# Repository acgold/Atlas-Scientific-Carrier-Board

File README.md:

# Atlas Scientific Carrier Board

This repository has Gerber files and a KiCad file for an Atlas Scientific chip carrier board. This board was designed to work with a Mayfly data logger from https://www.envirodiy.org/. Solder on female headers to plug in the sensor chips and inline voltage isolators. Voltage isolators are necessary, but you could use some jumper wires if you don't want to use a voltage isolator. The "EN" and "GND" at the top left allow you to attach a two-pin connector and set the voltage isolators to energy-saving mode (untested). A grove socket can be soldered onto the top of the board to allow easy communication using a grove cable. BNC connectors that connect to the sensors directly can be soldered on the bottom of the board, or use another three-pin connector. Three of these boards cost about $25 at https://oshpark.com/.

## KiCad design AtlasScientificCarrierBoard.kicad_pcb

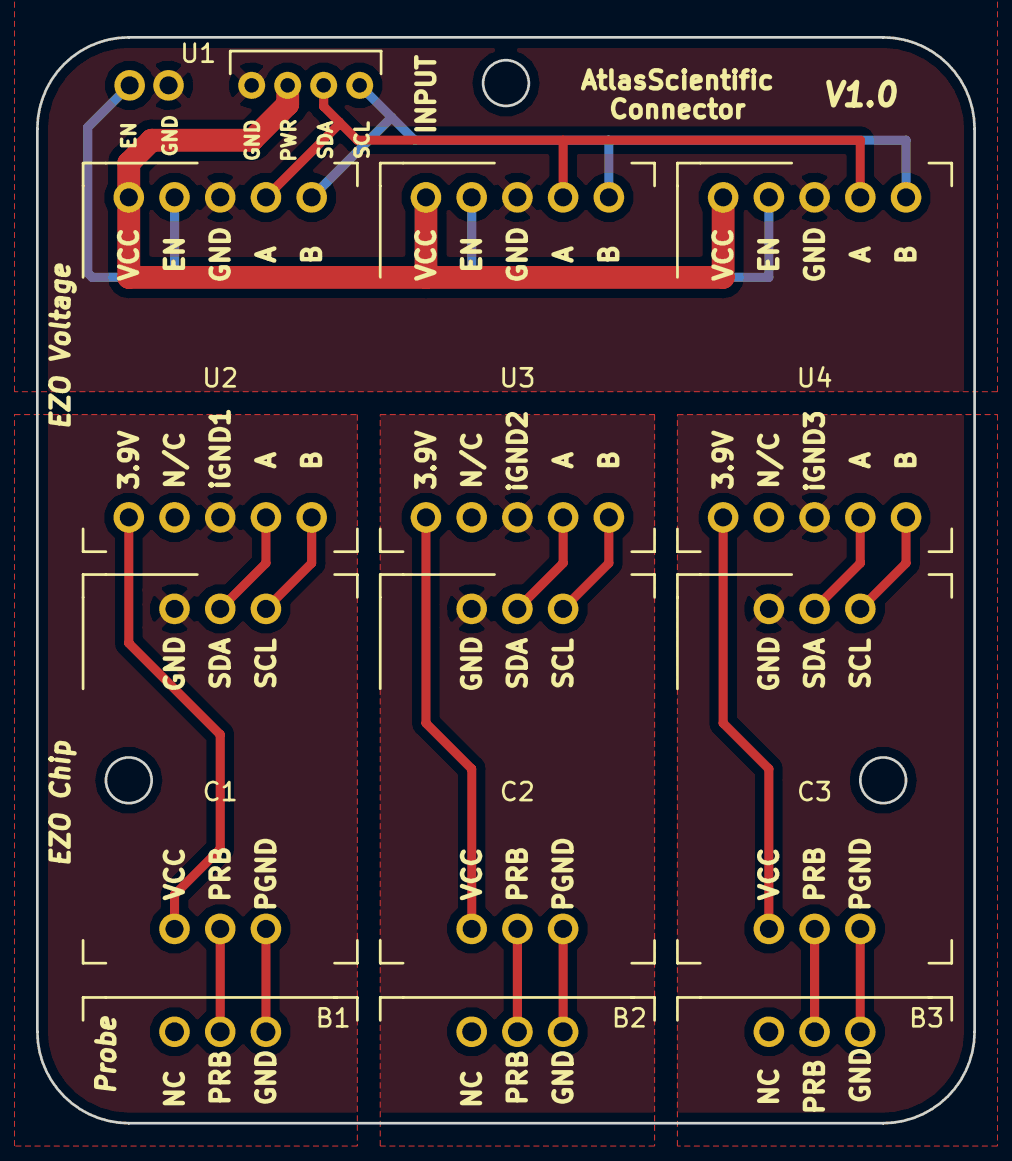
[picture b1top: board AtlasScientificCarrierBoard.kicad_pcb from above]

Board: 2 copper layers, 52.1 x 60.3 mm, 10 parts (0 on the bottom side), 23 nets.

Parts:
B1, B2, B3: BNCConnect; BNC
C1, C2, C3: EZOChip; EZOChip_2
U1: Input
U2, U3, U4: EZOVoltage

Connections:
unnamed: B1.2, C1.5
unnamed: B1.3, C1.6
unnamed: B2.2, C2.5
unnamed: B2.3, C2.6
unnamed: B3.2, C3.5
unnamed: B3.3, C3.6
unnamed: C1.1, U2.8
unnamed: C1.2, U2.9
unnamed: C1.3, U2.10
unnamed: C1.4, U2.6
unnamed: C2.1, U3.8
unnamed: C2.2, U3.9
unnamed: C2.3, U3.10
unnamed: C2.4, U3.6
unnamed: C3.1, U4.8
unnamed: C3.2, U4.9
unnamed: C3.3, U4.10
unnamed: C3.4, U4.6
unnamed: U1.1, U1.6, U2.3, U3.3, U4.3
unnamed: U1.2, U2.1, U3.1, U4.1
unnamed: U1.3, U2.4, U3.4, U4.4
unnamed: U1.4, U2.5, U3.5, U4.5
unnamed: U1.5, U2.2, U3.2, U4.2
